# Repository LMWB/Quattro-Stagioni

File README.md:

# Quattro-Stagioni
RTD-Sensor Breakoutboard and C-Library

# Abstract
RTD stands for Resistance Temperature Detector. Most common used versions are PT100, PT1000 and KTY.

RTD Messverfahren werden von IC's implementiert wie z.B. der ADS124 von TI. Mit ca. 10€ sind diese jedoch verhaeltnismaessig preisintensiv.
RDT-Sensoren werden typischerweise mit einem konstanten Strom um die 1mA beaufschlagt und der daraus resultierende Spannungsfall wird gemessen.
Die spezifische Kennklienie gibt Aufschluss über die vorherrschende Temperatur.
Dieses einfache Messverfahren hat den Nachteil, dass im interesanten Wertebereich von ca. 0 bis 70 •C nur ein sehr geringer Spannungshub von ca. 250 mV entsteht (abhaengig vom gewaehlten erregerstrom, je kleiner um so besser um die Eigenerwaermung im Sensor zu vermeiden). Die Kurve R = f(T) ist also sehr flach. 

Es erfordert einen sehr hochauflösenden ADC (16bit oder mehr) um einen entsprechenden Ausschlag zu messen.
Ein weitere Nachteil ist, dass die Referenzspannung des ADC nur in einem sehr kleinen Arbeitsbereich verwendet wird.

Abhilfe schafft eine einfache Verstärkerschaltung mit einem unipolarem Operationsverstaerker.
Dieses hier vorgestellte analoge Eingangsstufe kann auch für andere physikalische Größen verwendet werden wie z.B. Ladekennlinie moderne Akkus welche von Natur aus sehr flach sind.

- blue without gain amplifier
- green with gain amplifier

Die oben beschriebene Schaltung wurde im Formfaktor eines vereinfachten Arduino-Shield realisiert. Die Platine implementier 4 Messkanaele da ein 4-fach OP verwendet wurde.

# Documentation
[PCB Design and Gerber Files](/Hardware/)  
[Simulations and Models](/Simulations/)  
[Microcontroller based C-Code](/Software/)  
[BOM and costs](/Hardware/)  
[Results and Discussion](/Testing/)  

# Todo
- translate to english
- solder PCB
- testing
- reference measurement
- add CAN or Modbus to PCB

# Some Web Links
[Widerstandsthermometer / Pt100 Fühler](https://www.tcgmbh.de/widerstandsthermometer/pt100-fuehler.html?gad_source=1&gclid=EAIaIQobChMIzJ2AwLC6hwMVt5hQBh2AcgBmEAAYAiAAEgKx2PD_BwE)  
[Wissenswertes über RTDs](https://www.te.com/de/products/sensors/temperature-sensors/resources/understanding-rtds.html)  
[ADS124 at mouser.com](https://www.mouser.de/ProductDetail/Texas-Instruments/ADS124S08IPBSR?qs=Bho%2FbeBaDEw8zBU%2F9K2heg%3D%3D)  

# Sorces
Wolf-Dieter Schmidt, Sensorschaltungstechnik, Elektronik 8, Vogel Fachbuch, Linearisierung von Silizium-Widerstandssensoren, S. 71

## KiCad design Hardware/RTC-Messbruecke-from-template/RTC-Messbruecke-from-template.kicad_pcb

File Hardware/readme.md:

# Hardware Description
todo
# BOM and costs
Estimation of costs for RDC Sensor Board with four channels. Prizing from mouser.com 100 pieces. This calculation considers only parts relevant for the measurement bridge to make it comparable.  

| Part                             | Quantities      | Cost per unit (Euro) | Cost total |
| -------------------------------- | -----------     | -----------          | ---------- |
| LM324 Operational Amplifier      | 1               | 0,08                 | 0.08  |
| REF195 Reference Voltage Source  | 1               | 3,11                 | 3.11  |
| Decoupling Capacity              | 5               | 0,07 (WE)            | 0,35  |
| Resistor 1%                      | 16              | 0,01 (Vishay)        | 0,16  |

In Total: 3.7 Euro where the reference voltage is the most expensive part. 

In comparison to a quite popular approach using the ADS124S08 integrated RCD Measurement ADC from Texas Instruments. 

| Part                             | Quantities      | Cost per unit (Euro) | Cost total |
| -------------------------------- | -----------     | -----------          | ---------- |
| ADS124s 24-Bit ADC               | 1               | 6,55                 |            |
| Decoupling Capacity              |                 |                      |            |
| Resistor 1%                      |                 |                      |            |

In Total: 6,55 Euro  
With LM324 sampling is much faster since its four channels in parallel where as the ADS124 has to multiplex, but with the ADS124 approach data is already in digital format.

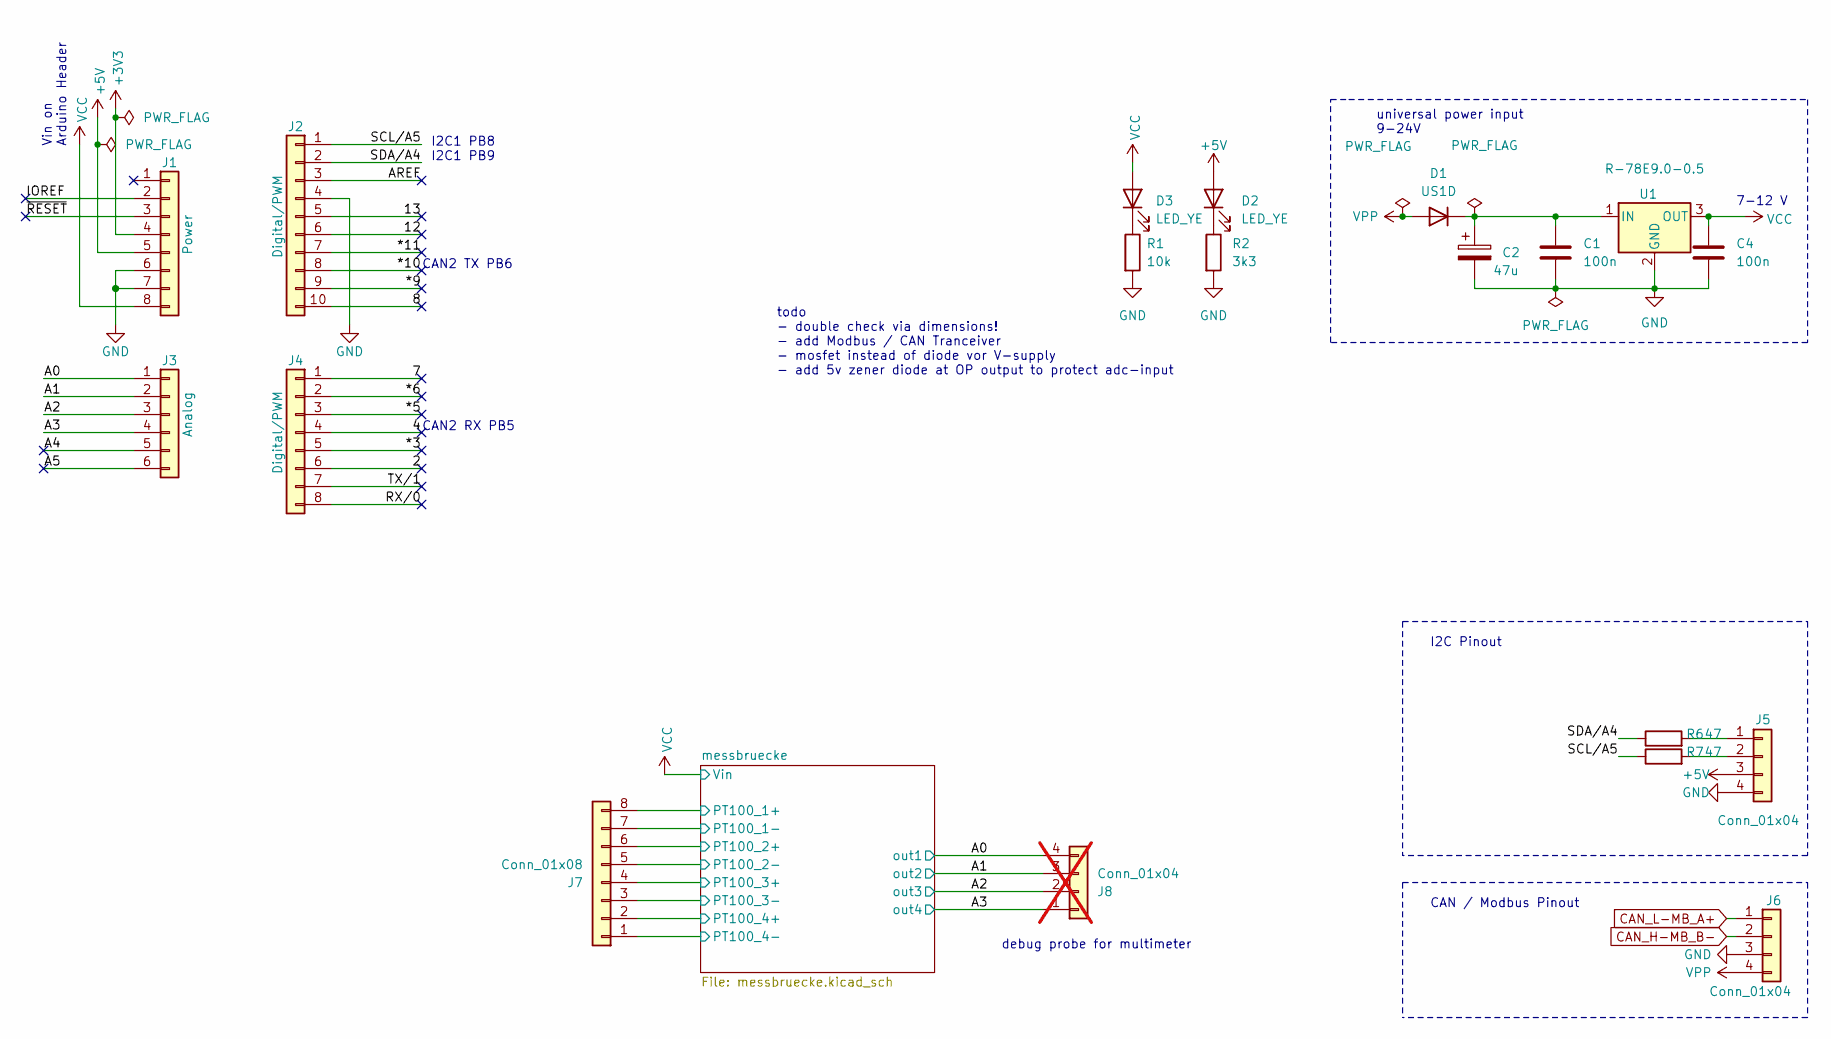
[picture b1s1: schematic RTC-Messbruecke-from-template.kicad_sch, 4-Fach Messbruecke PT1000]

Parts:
C1, C4: 100n; C_1206_3216Metric_Pad1.33x1.80mm_HandSolder
C2: 47u; CP_Elec_10x12.5
D1: US1D; D_SMA
D2, D3: LED_YE; LED_1210_3225Metric_Pad1.42x2.65mm_HandSolder
J1: Power; PinSocket_1x08_P2.54mm_Vertical
J2: Digital/PWM; PinSocket_1x10_P2.54mm_Vertical
J3: Analog; PinSocket_1x06_P2.54mm_Vertical
J4: Digital/PWM; PinSocket_1x08_P2.54mm_Vertical
J5: Conn_01x04; PinHeader_1x04_P2.54mm_Vertical
J6: Conn_01x04; TerminalBlock_Phoenix_MPT-0,5-4-2.54_1x04_P2.54mm_Horizontal
J7: Conn_01x08; TerminalBlock_Phoenix_MPT-0,5-8-2.54_1x08_P2.54mm_Horizontal
J8: Conn_01x04; TerminalBlock_Phoenix_MPT-0,5-4-2.54_1x04_P2.54mm_Horizontal; not fitted
R1: 10k; R_1206_3216Metric_Pad1.30x1.75mm_HandSolder
R2: 3k3; R_1206_3216Metric_Pad1.30x1.75mm_HandSolder
R6, R7: 47; R_1206_3216Metric_Pad1.30x1.75mm_HandSolder
U1: R-78E9.0-0.5; Converter_DCDC_RECOM_R-78E-0.5_THT

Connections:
+3V3: J1.4
+5V: D2.2 (A), J1.5, J5.3; also elsewhere on the board
/2: J4.6
/4: J4.4
/7: J4.1
/8: J2.10
/12: J2.6
/13: J2.5
/*3: J4.5
/*5: J4.3
/*6: J4.2
/*9: J2.9
/*10: J2.8
/*11: J2.7
/A0: J3.1, J8.4; also elsewhere on the board
/A1: J3.2, J8.3; also elsewhere on the board
/A2: J3.3, J8.2; also elsewhere on the board
/A3: J3.4, J8.1; also elsewhere on the board
/A4: J3.5
/A5: J3.6
/AREF: J2.3
/IOREF: J1.2
/RX/0: J4.8
/SCL/A5: J2.1, R7.1
/SDA/A4: J2.2, R6.1
/TX/1: J4.7
/messbruecke/PT100_1+: J7.8; also elsewhere on the board
/messbruecke/PT100_2+: J7.6; also elsewhere on the board
/messbruecke/PT100_3+: J7.4; also elsewhere on the board
/messbruecke/PT100_4+: J7.2; also elsewhere on the board
/~RESET: J1.3
CAN_H-MB_B-: J6.2
CAN_L-MB_A+: J6.1
GND: C1.2, C2.2, C4.2, J1.6, J1.7, J2.4, J5.4, J6.3, J7.1, J7.3, J7.5, J7.7, R1.2, R2.2, U1.2 (GND); also elsewhere on the board
unnamed: C1.1, C2.1, D1.1 (K), U1.1 (IN)
unnamed: D2.1 (K), R2.1
unnamed: D3.1 (K), R1.1
unnamed: J5.1, R6.2
unnamed: J5.2, R7.2
VCC: C4.1, D3.2 (A), J1.8, U1.3 (OUT); also elsewhere on the board
VPP: D1.2 (A), J6.4

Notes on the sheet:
Vin on Arduino Header
I2C1 PB8 I2C1 PB9
7-12 V
CAN / Modbus Pinout
CAN2 RX PB5
CAN2 TX PB6
I2C Pinout
todo - double check via dimensions! - add Modbus / CAN Tranceiver - mosfet instead of diode vor V-supply - add 5v zener diode at OP output to protect adc-input
debug probe for multimeter
universal power input 9-24V

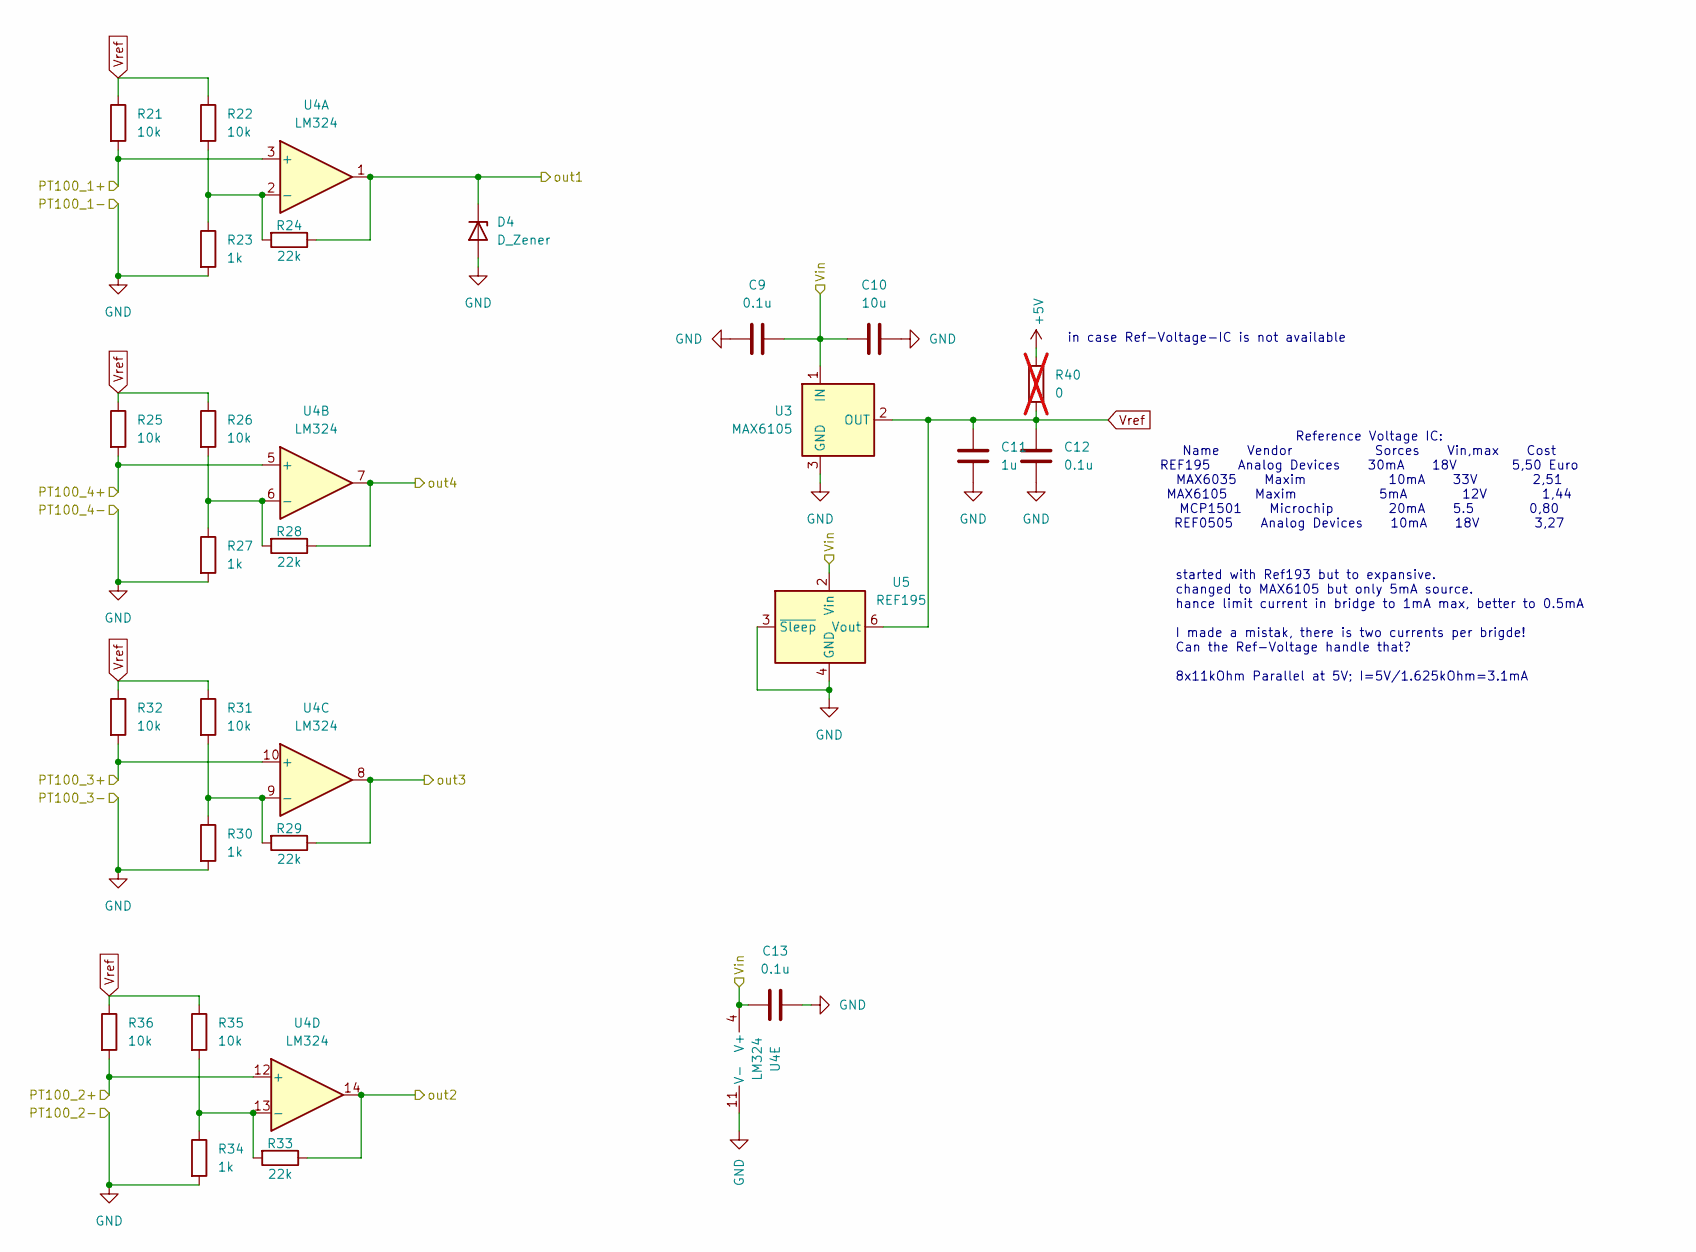
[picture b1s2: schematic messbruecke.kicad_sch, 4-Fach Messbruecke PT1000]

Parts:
C9, C12, C13: 0.1u; C_1206_3216Metric
C10: 10u; C_1206_3216Metric
C11: 1u; C_1206_3216Metric
D4: D_Zener; D_1206_3216Metric
R21, R22, R25, R26, R31, R32, R35, R36: 10k; R_1206_3216Metric
R23, R27, R30, R34: 1k; R_1206_3216Metric
R24, R28, R29, R33: 22k; R_1206_3216Metric
R40: 0; R_1206_3216Metric; not fitted
U3: MAX6105; SOT-23
U4: LM324; SOIC-14_3.9x8.7mm_P1.27mm
U5: REF195; SOIC-8_3.9x4.9mm_P1.27mm

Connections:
+5V: R40.1; also elsewhere on the board
/A0: D4.1 (K), R24.1, U4.1; also elsewhere on the board
/A1: R33.1, U4.14; also elsewhere on the board
/A2: R29.1, U4.8; also elsewhere on the board
/A3: R28.1, U4.7; also elsewhere on the board
/messbruecke/PT100_1+: R21.2, U4.3 (+); also elsewhere on the board
/messbruecke/PT100_2+: R36.2, U4.12 (+); also elsewhere on the board
/messbruecke/PT100_3+: R32.2, U4.10 (+); also elsewhere on the board
/messbruecke/PT100_4+: R25.2, U4.5 (+); also elsewhere on the board
GND: C9.2, C10.2, C11.2, C12.2, C13.2, D4.2 (A), R23.2, R27.2, R30.2, R34.2, U3.3 (GND), U4.11 (V-), U5.3 (~Sleep), U5.4 (GND); also elsewhere on the board
unnamed: R22.2, R23.1, R24.2, U4.2 (-)
unnamed: R26.2, R27.1, R28.2, U4.6 (-)
unnamed: R29.2, R30.1, R31.2, U4.9 (-)
unnamed: R33.2, R34.1, R35.2, U4.13 (-)
VCC: C9.1, C10.1, C13.1, U3.1 (IN), U4.4 (V+), U5.2 (Vin); also elsewhere on the board
Vref: C11.1, C12.1, R21.1, R22.1, R25.1, R26.1, R31.1, R32.1, R35.1, R36.1, R40.2, U3.2 (OUT), U5.6 (Vout)

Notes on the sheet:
in case Ref-Voltage-IC is not available
started with Ref193 but to expansive. changed to MAX6105 but only 5mA source. hance limit current in bridge to 1mA max, better to 0.5mA I made a mistak, there is two currents per brigde! Can the Ref-Voltage handle that? 8x11kOhm Parallel at 5V; I=5V/1.625kOhm=3.1mA
Reference Voltage IC: Name Vendor Sorces Vin,max Cost REF195 Analog Devices 30mA 18V 5,50 Euro MAX6035 Maxim 10mA 33V 2,51 MAX6105 Maxim 5mA 12V 1,44 MCP1501 Microchip 20mA 5.5 0,80 REF0505 Analog Devices 10mA 18V 3,27

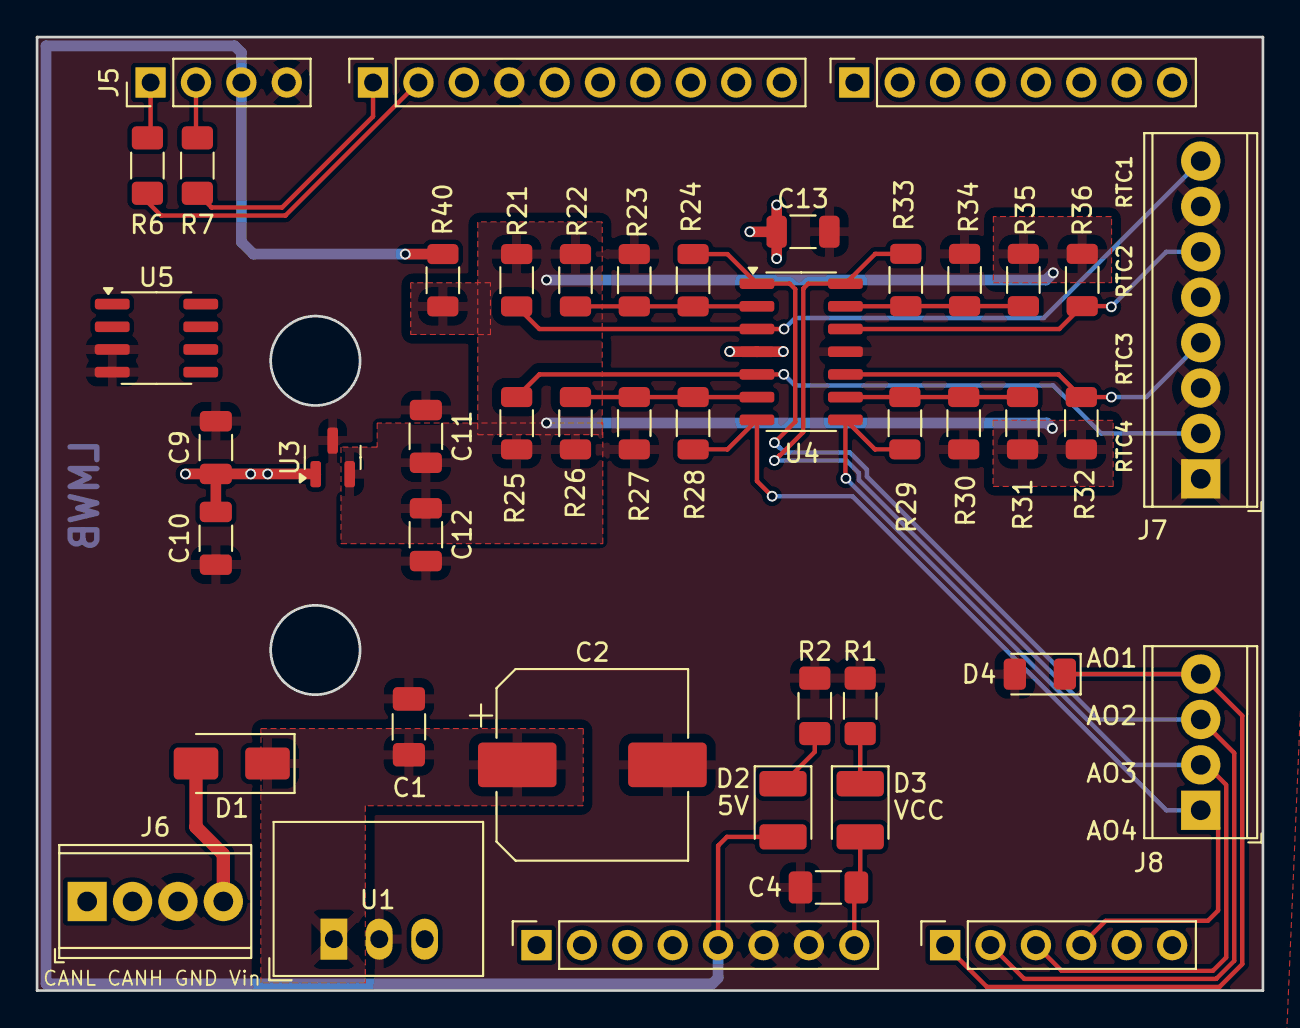
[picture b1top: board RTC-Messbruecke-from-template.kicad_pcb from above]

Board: 2 copper layers, 68.6 x 53.3 mm, 45 parts (0 on the bottom side), 24 nets.

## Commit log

2024-08-20 README.md aktualisieren
2024-08-22 test.txt aktualisieren
2024-08-22 hardware.md aktualisieren
2024-08-25 added a lot of files
2024-09-02 added picture intext, renamed folder
2024-09-02 changed ltspice picture results
2024-09-02 make shure LTspice simulation will work
2024-09-02 make shure octave simulation will work, deleted unnecessary files
2024-09-02 added pic to text
2024-09-02 replaced readme for hardware text file
2024-09-02 changed back to readme
2024-09-02 modified readme
2024-09-02 added picture of schematic
2024-09-02 clear gitignor, deleted kicad backups
2024-09-02 typo
2024-09-23 added test results and simulations
2024-09-23 first simple plot of test results
2024-09-23 smoothing measured data improves plots
2024-10-28 added REF-195 as alternativ voltage reference
2024-11-04 update gitignore
2024-11-11 added images and text to results-readme
2024-12-03 added BOM
2024-12-04 added images
2024-12-05 modifed readme (testing&results)
2024-12-05 modifed readme
2024-12-05 modifed readme (hardware)
2025-01-13 rename readme to README
2025-01-16 spice model to map from -20..+80 deg.C
